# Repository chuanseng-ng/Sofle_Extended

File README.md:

# Sofle_Extended
 Sofle Split Keyboard Design but with extra row & column added

## Details
- Added extra row and column to each side of Sofle split keyboard for more flexibility
- Micro-controller used will have to be Elite-C due to extra ports needed for row and column

## Version history
- V1.0: Initial fabricated PCB with tested functions
- V1.1: Modified PCB component placement to improve aesthetics and feasibility

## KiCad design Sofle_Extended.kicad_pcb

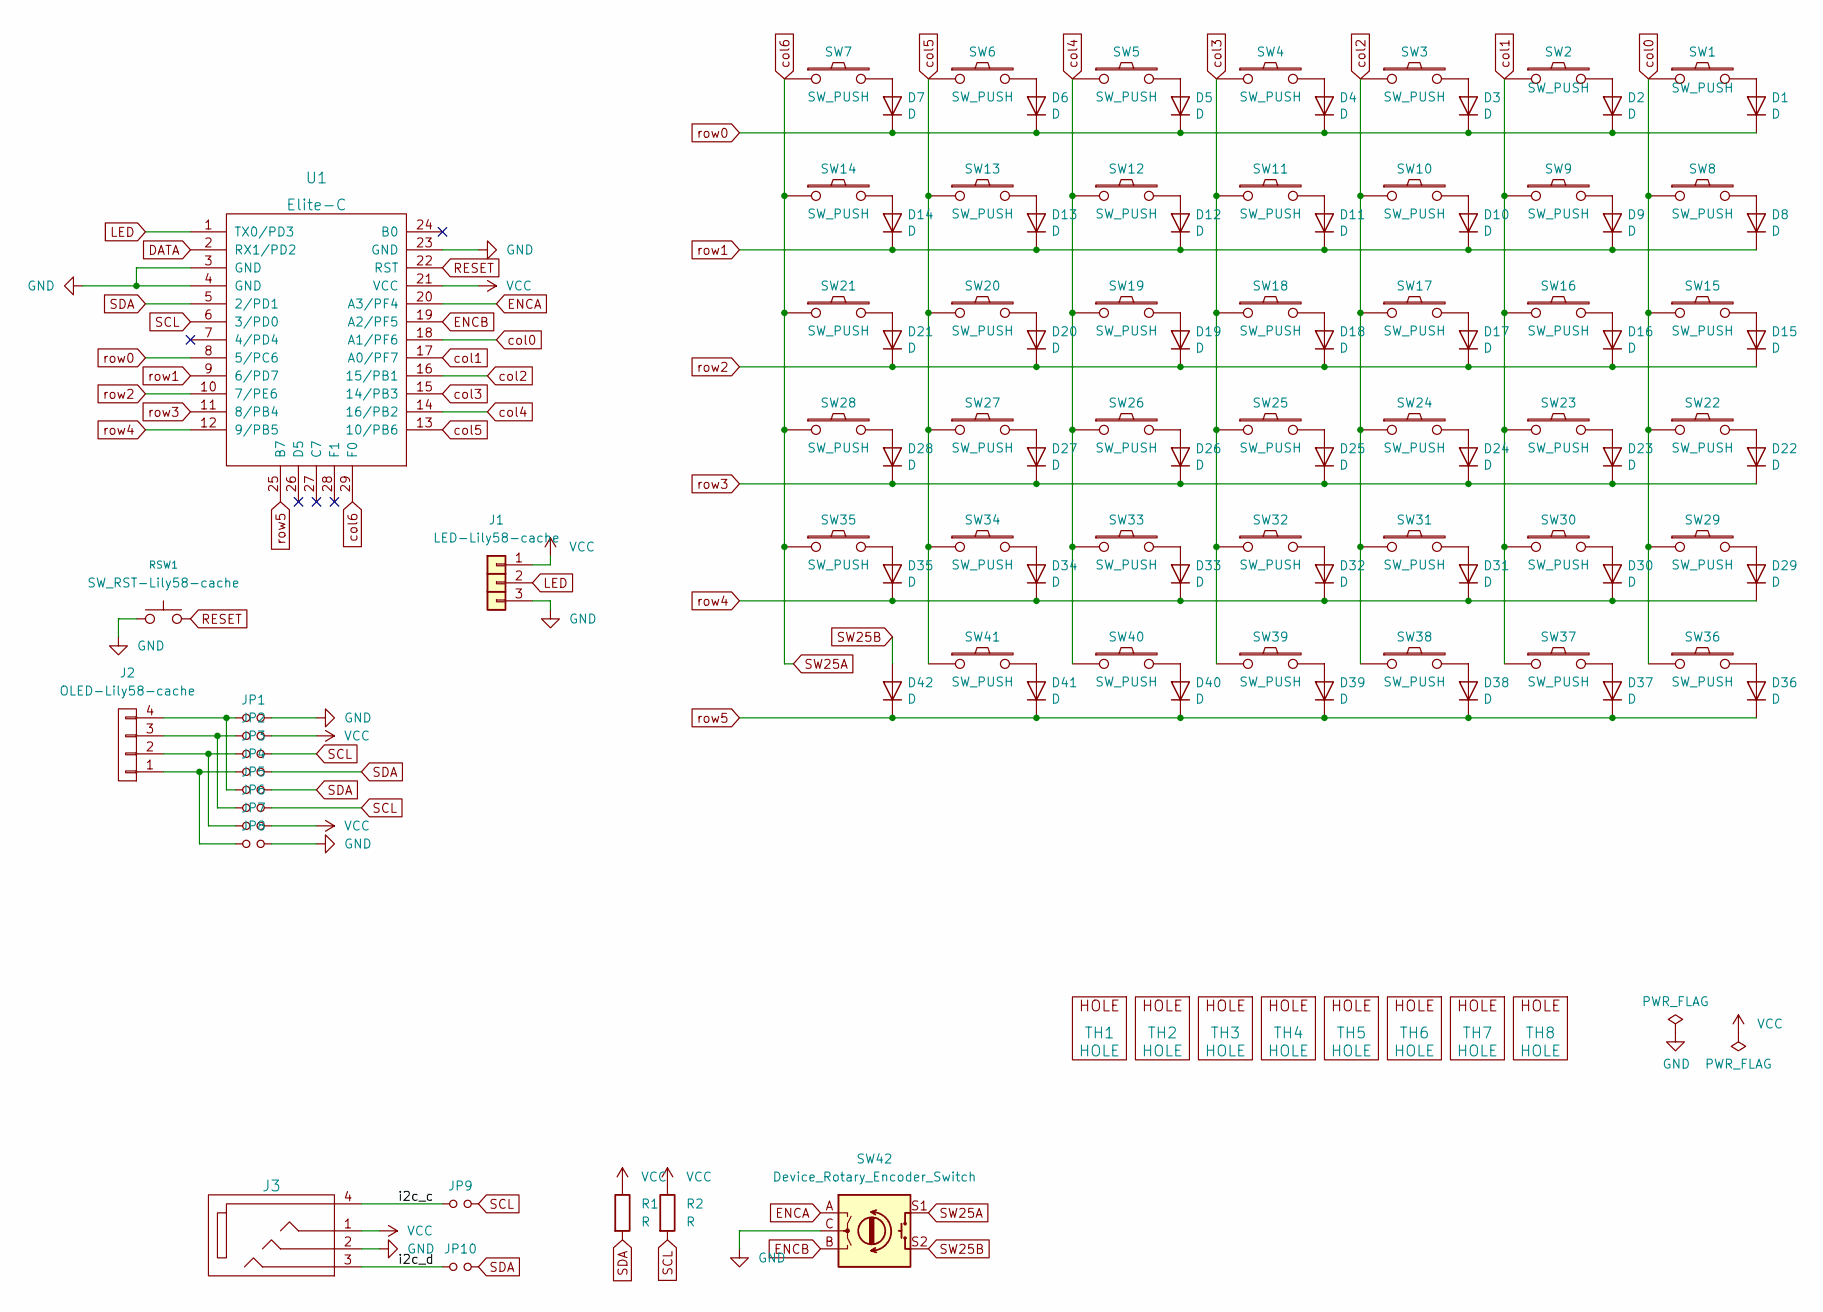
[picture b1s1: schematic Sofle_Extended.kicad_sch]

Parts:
D1, D2, D3, D4, D5, D6, D7, D8, D9, D10, D11, D12, D13, D14, D15, D16, D17, D18, D19, D20, D21, D22, D23, D24, D25, D26, D27, D28, D29, D30, D31, D32, D33, D34, D35, D36, D37, D38, D39, D40, D41, D42: D; Diode_SOD123
J1: LED-Lily58-cache; LED
J2: OLED-Lily58-cache; OLED_4Pin
J3: SofleKeyboard-rescue_MJ-4PP-9-Lily58-cache-Lily58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; MJ-4PP-9
JP1, JP2, JP3, JP4, JP5, JP6, JP7, JP8, JP9, JP10: Device_Jumper_NO_Small; Jumper
R1, R2: R; R_1206_DoubleSided
RSW1: SW_RST-Lily58-cache; TACT_SWITCH_TVBP06
SW1, SW2, SW3, SW4, SW5, SW6, SW7, SW8, SW9, SW10, SW11, SW12, SW13, SW14, SW15, SW16, SW17, SW18, SW19, SW20, SW21, SW22, SW23, SW24, SW25, SW26, SW27, SW28, SW29, SW30, SW31, SW32, SW33, SW34, SW35, SW36, SW37, SW38, SW39, SW40: SW_PUSH; CherryMX_Hotswap
SW41: SW_PUSH; CherryMX_Hotswap_1.5
SW42: Device_Rotary_Encoder_Switch; RotaryEncoder_Alps_EC11E-Switch_Vertical_H20mm-keebio_modif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
TH1, TH2: HOLE; M2_HOLE_PCB
TH3, TH4, TH5, TH6, TH7, TH8: HOLE; HOLE_M2_TH
U1: Elite-C

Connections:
/i2c_c: J3.4, JP9.1
/i2c_d: J3.3, JP10.1
DATA: U1.2 (RX1/PD2)
ENCA: SW42.A, U1.20 (A3/PF4)
ENCB: SW42.B, U1.19 (A2/PF5)
GND: J1.3, J3.2, JP1.2, JP8.2, RSW1.1, SW42.C, U1.3 (GND), U1.4 (GND), U1.23 (GND)
LED: J1.2, U1.1 (TX0/PD3)
unnamed: D1.2 (A), SW1.2
unnamed: D2.2 (A), SW2.2
unnamed: D3.2 (A), SW3.2
unnamed: D4.2 (A), SW4.2
unnamed: D5.2 (A), SW5.2
unnamed: D6.2 (A), SW6.2
unnamed: D7.2 (A), SW7.2
unnamed: D8.2 (A), SW8.2
unnamed: D9.2 (A), SW9.2
unnamed: D10.2 (A), SW10.2
unnamed: D11.2 (A), SW11.2
unnamed: D12.2 (A), SW12.2
unnamed: D13.2 (A), SW13.2
unnamed: D14.2 (A), SW14.2
unnamed: D15.2 (A), SW15.2
unnamed: D16.2 (A), SW16.2
unnamed: D17.2 (A), SW17.2
unnamed: D18.2 (A), SW18.2
unnamed: D19.2 (A), SW19.2
unnamed: D20.2 (A), SW20.2
unnamed: D21.2 (A), SW21.2
unnamed: D22.2 (A), SW22.2
unnamed: D23.2 (A), SW23.2
unnamed: D24.2 (A), SW24.2
unnamed: D25.2 (A), SW25.2
unnamed: D26.2 (A), SW26.2
unnamed: D27.2 (A), SW27.2
unnamed: D28.2 (A), SW28.2
unnamed: D29.2 (A), SW29.2
unnamed: D30.2 (A), SW30.2
unnamed: D31.2 (A), SW31.2
unnamed: D32.2 (A), SW32.2
unnamed: D33.2 (A), SW33.2
unnamed: D34.2 (A), SW34.2
unnamed: D35.2 (A), SW35.2
unnamed: D36.2 (A), SW36.2
unnamed: D37.2 (A), SW37.2
unnamed: D38.2 (A), SW38.2
unnamed: D39.2 (A), SW39.2
unnamed: D40.2 (A), SW40.2
unnamed: D41.2 (A), SW41.2
unnamed: J2.1, JP4.1, JP8.1
unnamed: J2.2, JP3.1, JP7.1
unnamed: J2.3, JP2.1, JP6.1
unnamed: J2.4, JP1.1, JP5.1
RESET: RSW1.2, U1.22 (RST)
SCL: JP3.2, JP6.2, JP9.2, R2.2, U1.6 (3/PD0)
SDA: JP4.2, JP5.2, JP10.2, R1.2, U1.5 (2/PD1)
SW25A: SW7.1, SW14.1, SW21.1, SW28.1, SW35.1, SW42.S1, U1.29 (F0)
SW25B: D42.2 (A), SW42.S2
VCC: J1.1, J3.1, JP2.2, JP7.2, R1.1, R2.1, U1.21 (VCC)
col0: SW1.1, SW8.1, SW15.1, SW22.1, SW29.1, SW36.1, U1.18 (A1/PF6)
col1: SW2.1, SW9.1, SW16.1, SW23.1, SW30.1, SW37.1, U1.17 (A0/PF7)
col2: SW3.1, SW10.1, SW17.1, SW24.1, SW31.1, SW38.1, U1.16 (15/PB1)
col3: SW4.1, SW11.1, SW18.1, SW25.1, SW32.1, SW39.1, U1.15 (14/PB3)
col4: SW5.1, SW12.1, SW19.1, SW26.1, SW33.1, SW40.1, U1.14 (16/PB2)
col5: SW6.1, SW13.1, SW20.1, SW27.1, SW34.1, SW41.1, U1.13 (10/PB6)
row0: D1.1 (K), D2.1 (K), D3.1 (K), D4.1 (K), D5.1 (K), D6.1 (K), D7.1 (K), U1.8 (5/PC6)
row1: D8.1 (K), D9.1 (K), D10.1 (K), D11.1 (K), D12.1 (K), D13.1 (K), D14.1 (K), U1.9 (6/PD7)
row2: D15.1 (K), D16.1 (K), D17.1 (K), D18.1 (K), D19.1 (K), D20.1 (K), D21.1 (K), U1.10 (7/PE6)
row3: D22.1 (K), D23.1 (K), D24.1 (K), D25.1 (K), D26.1 (K), D27.1 (K), D28.1 (K), U1.11 (8/PB4)
row4: D29.1 (K), D30.1 (K), D31.1 (K), D32.1 (K), D33.1 (K), D34.1 (K), D35.1 (K), U1.12 (9/PB5)
row5: D36.1 (K), D37.1 (K), D38.1 (K), D39.1 (K), D40.1 (K), D41.1 (K), D42.1 (K), U1.25 (B7)

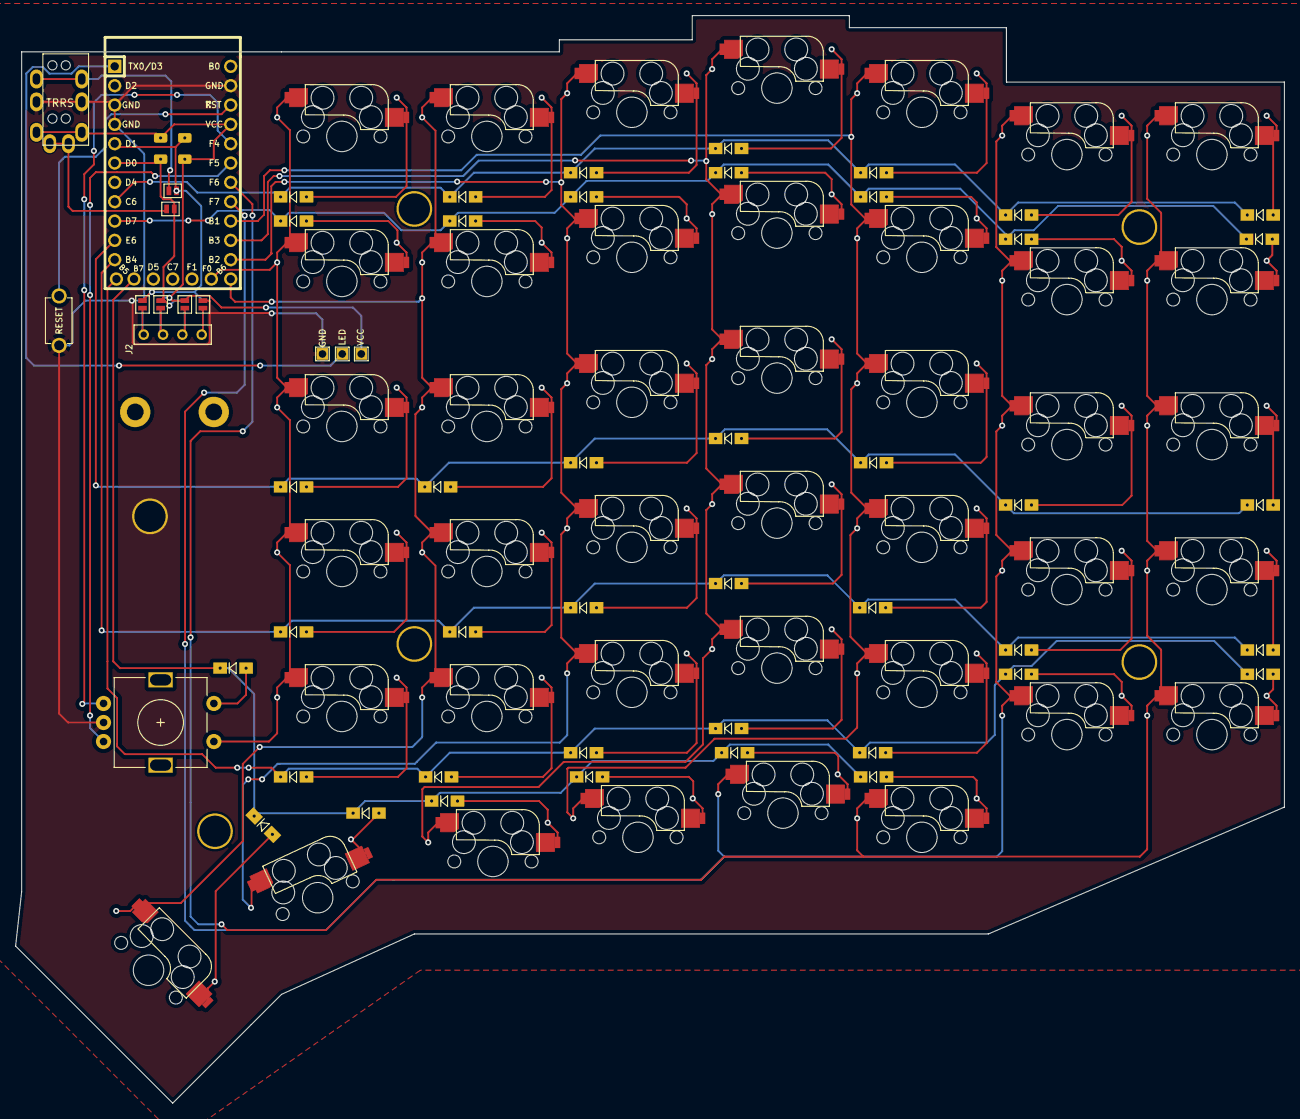
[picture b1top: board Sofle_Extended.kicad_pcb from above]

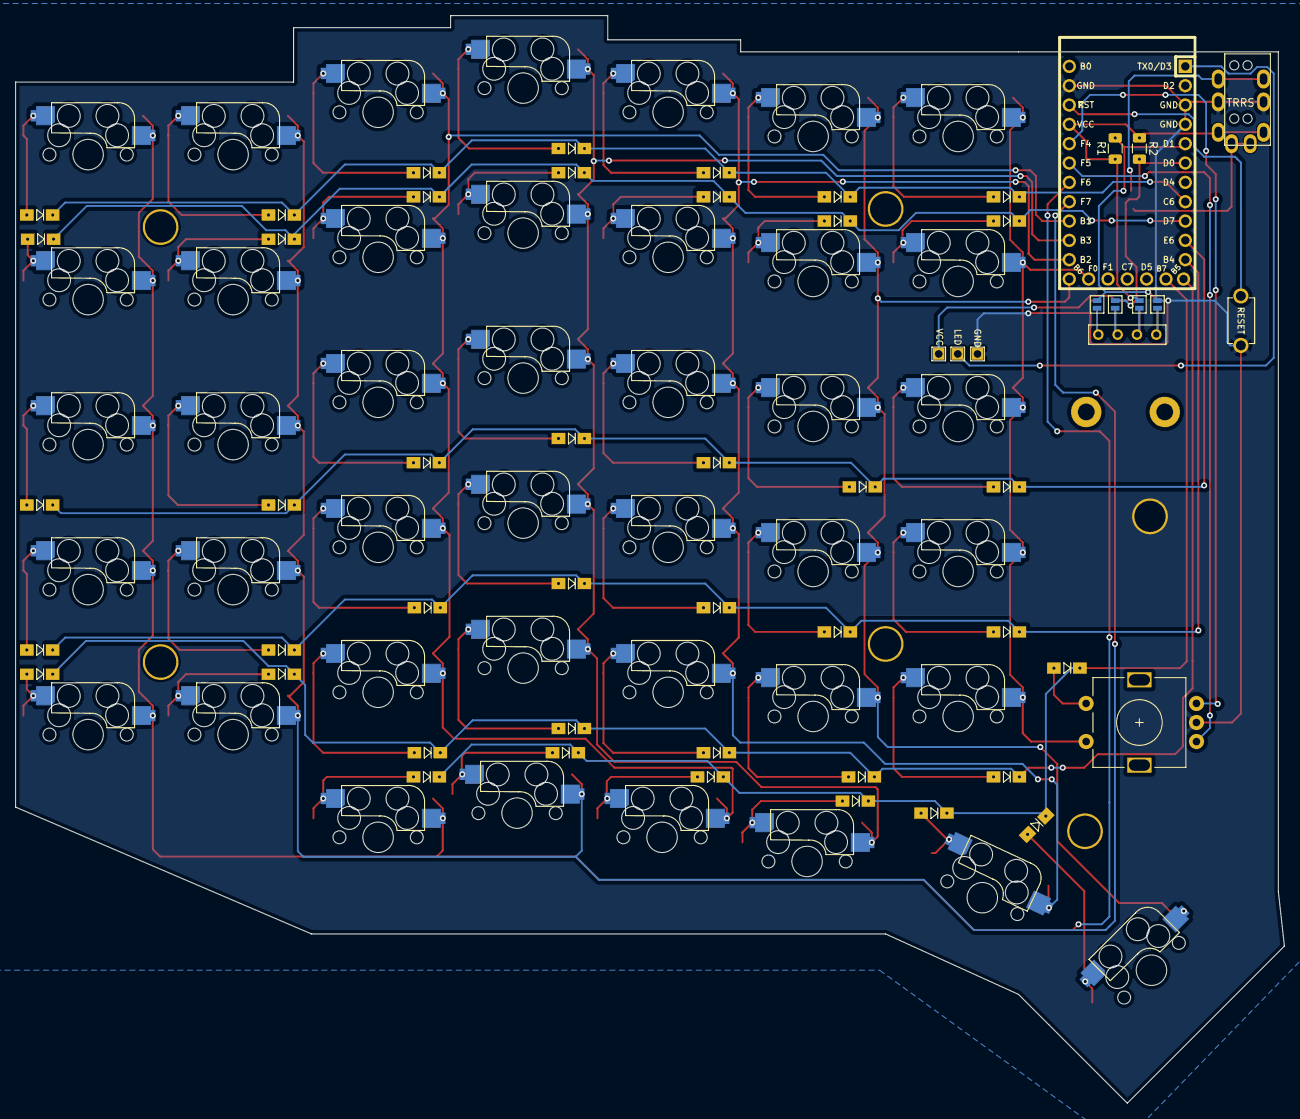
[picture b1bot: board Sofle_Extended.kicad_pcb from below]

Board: 2 copper layers, 166.7 x 142.9 mm, 109 parts (6 on the bottom side), 69 nets.

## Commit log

2022-08-09 Update README with details
2022-08-09 Initial commit for V1.0 design files
2022-08-09 Add V1.1 design files
